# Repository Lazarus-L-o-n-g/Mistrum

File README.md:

# Mistrum
Mistrum is a legendary czechoslovak functional clone of famous ZX-Spectrum, more details at [8bit-replicas.com](https://www.8bit-replicas.com)

# Repository content
Here you can find schematics, PCB, gerber files, BOMs, binary content for memories and some ideas for build a replica.

# Main parts
- Rerouted PCB for replica of Mistrum computer (less vias and no additional wiring)
- PCB with original routing (500+ vias and ca. 40 wires)**
- PCB for PAL color video generator replica
- PCB for EPROM card replica**
- PCB for newly designed keyboard (Cherry MX extended keyboard)
- PCB for newly designed adapter to analog RGBi SCART or VGA 15kHz color video output
- PCB for newly designed adapter to standard ZX Spectrum system connector**

** will come later

**All schematics and PCBs are made using KiCad.**

## Extended Cherry MX Keyboard

The newly designed extended Cherry MX Keyboard features:
- Mechanical Cherry MX switches
- ZX Spectrum compatibility
- Optional bus or external power supply (external is deafult for Mistrum)
- Extended to separate cursors keys, delete key and special Mistrum keys (key Mistrum, NMI and RESET), realized as logic switches
- Two LED indicators, optional (for example BOOT, DRIVE)
- Two PCBs - main board and mask
- Identical size and mounting holes as PMD-85 coputer keyboard

## Adapter to analog RGBi or VGA 15kHz video output

This adapter outputs an analog RGB signal or VGA signal (15kHz only). It is designed mainly for color video output to RGB SCART capable TV and provides the high quality color video output.

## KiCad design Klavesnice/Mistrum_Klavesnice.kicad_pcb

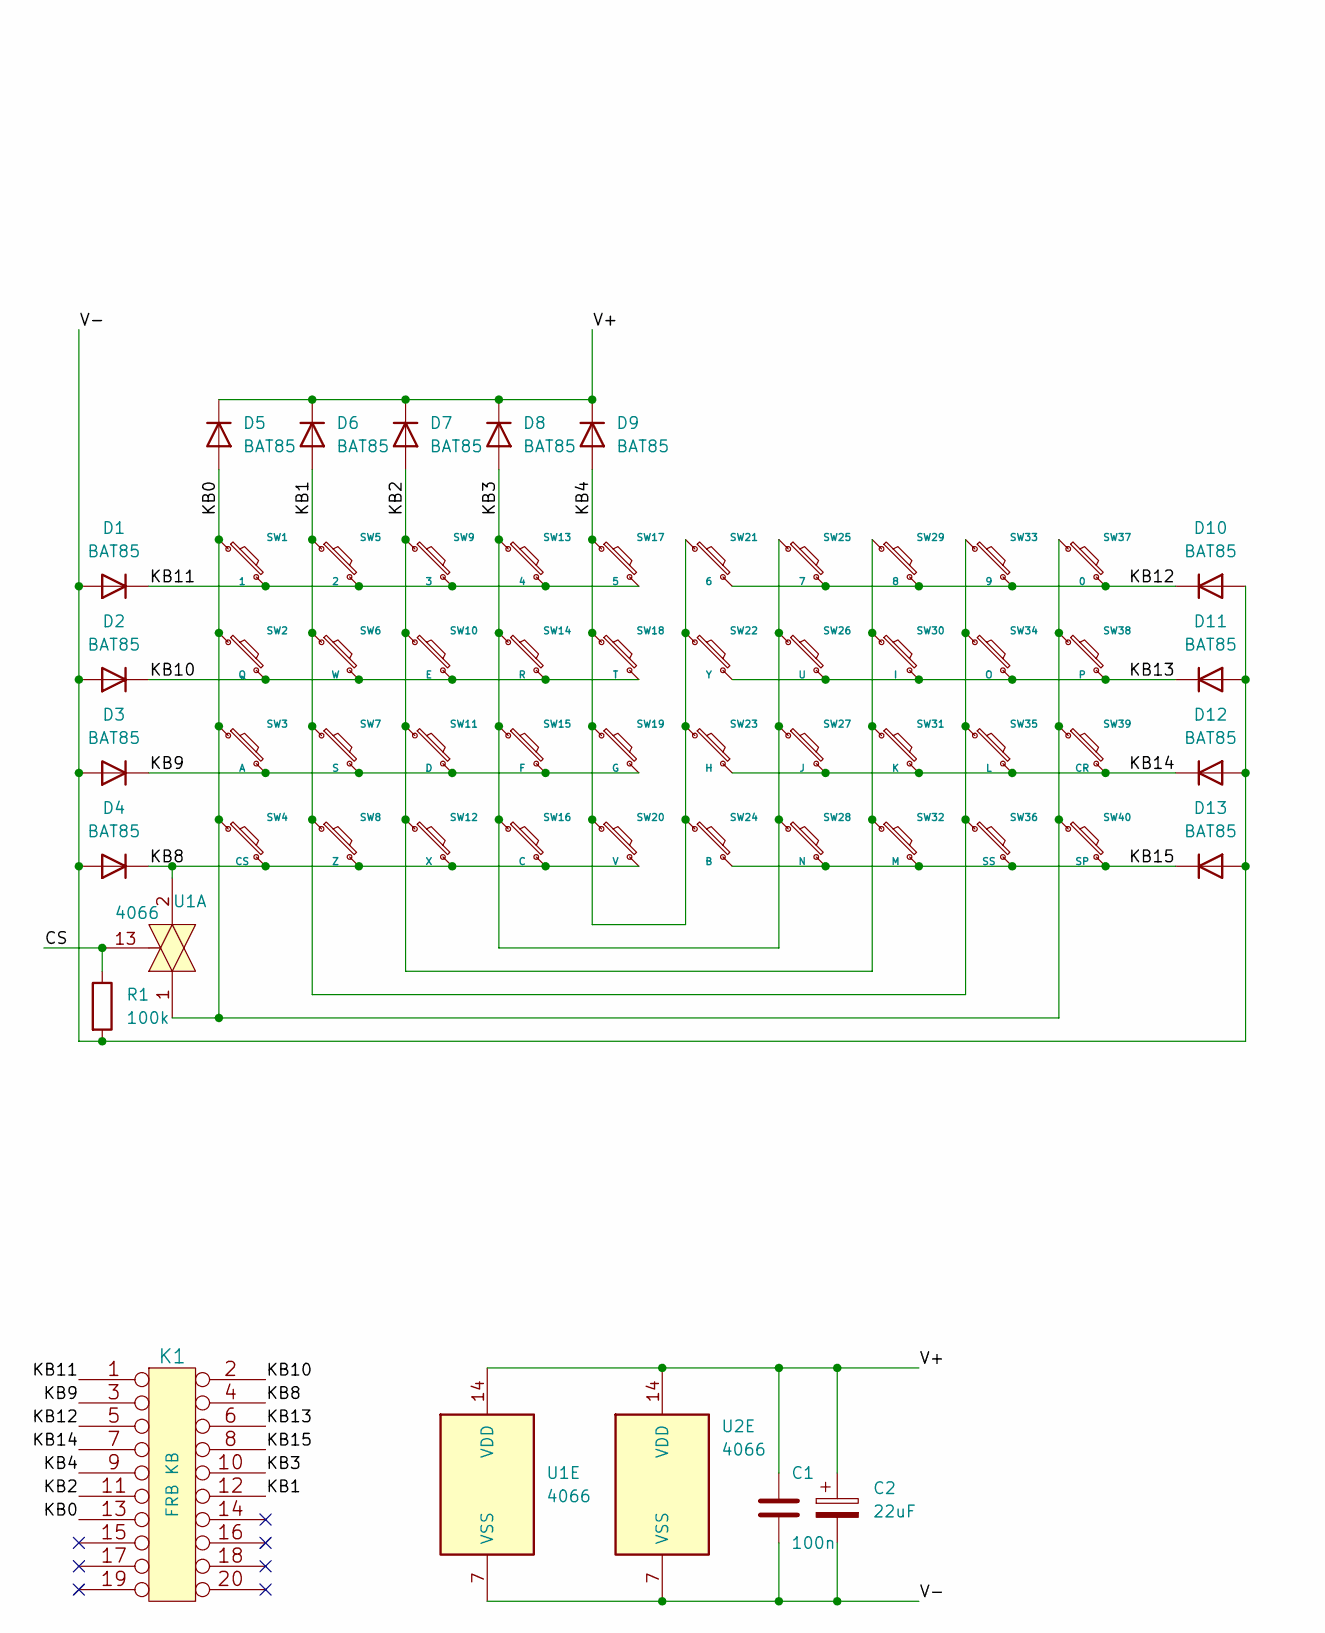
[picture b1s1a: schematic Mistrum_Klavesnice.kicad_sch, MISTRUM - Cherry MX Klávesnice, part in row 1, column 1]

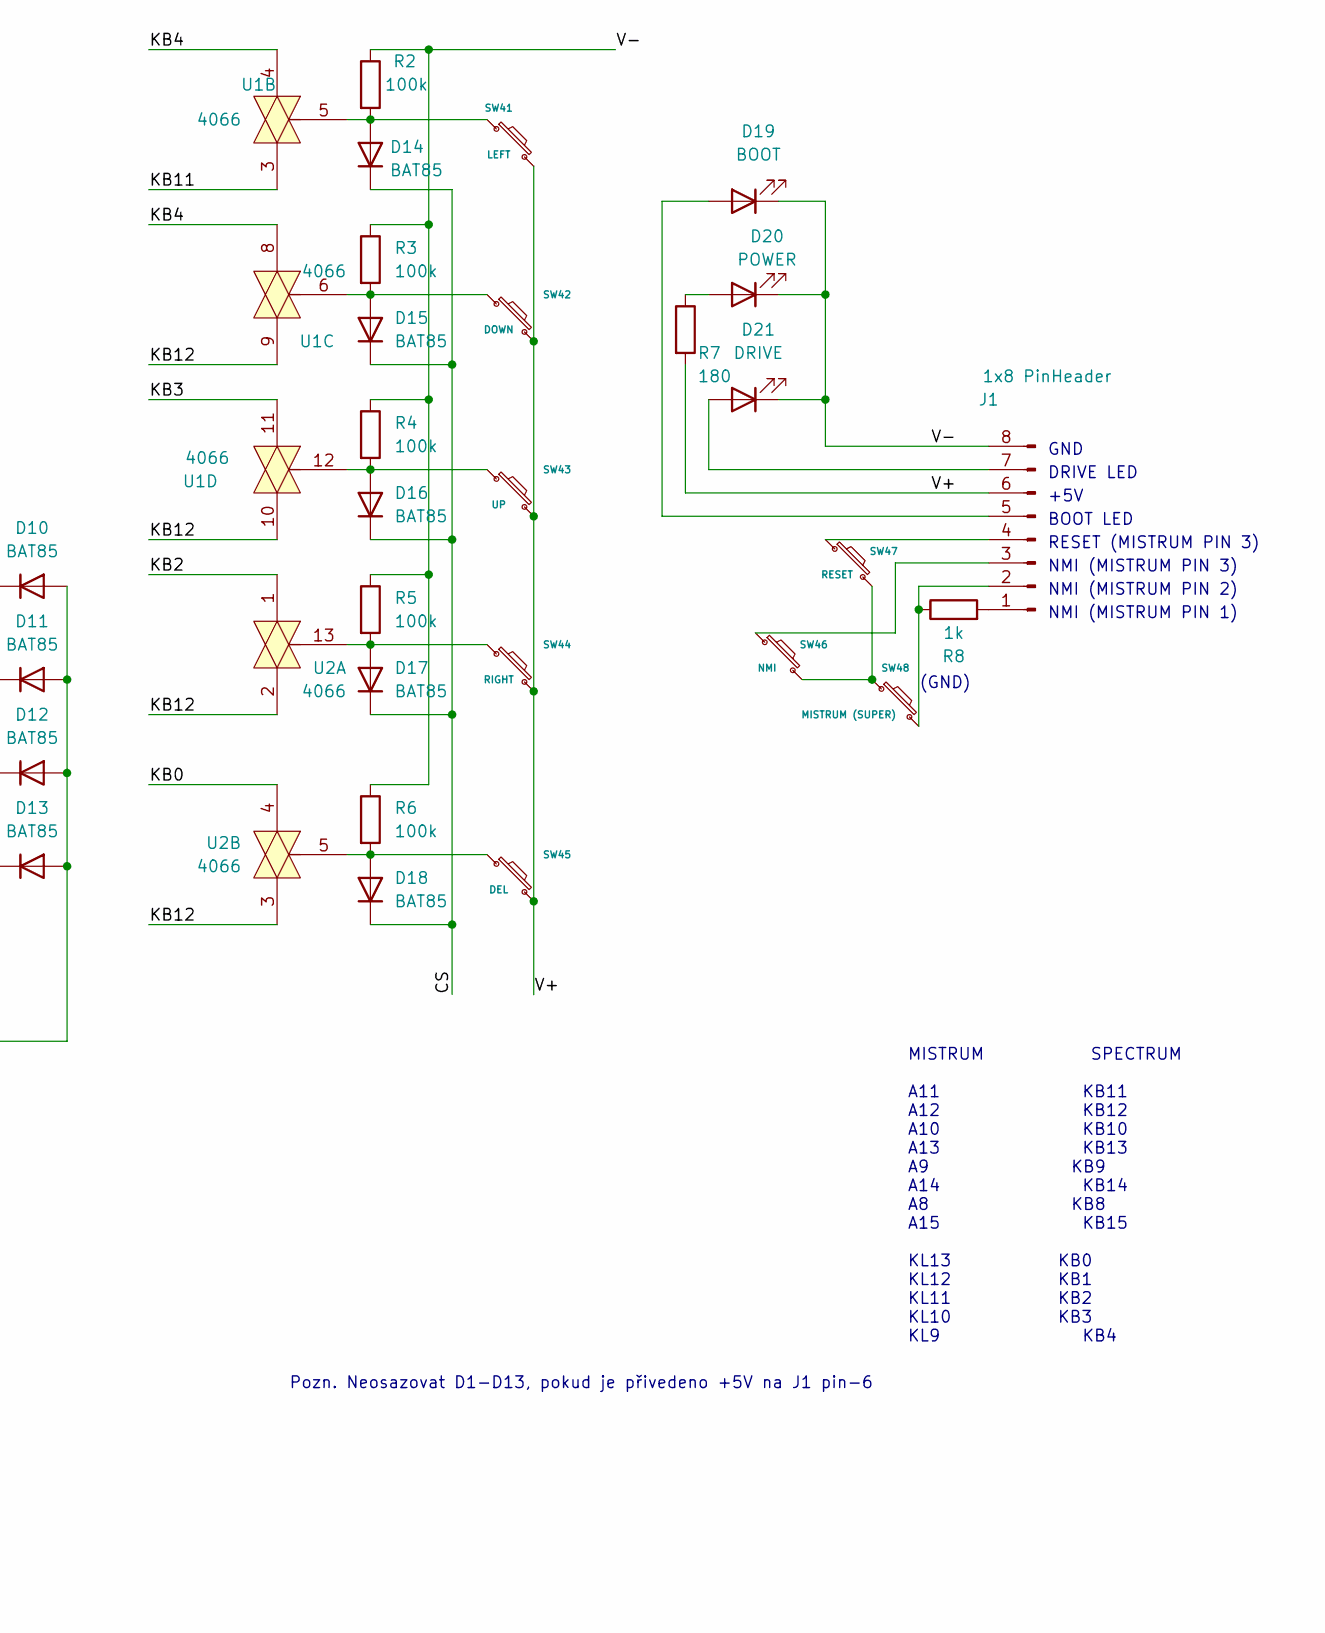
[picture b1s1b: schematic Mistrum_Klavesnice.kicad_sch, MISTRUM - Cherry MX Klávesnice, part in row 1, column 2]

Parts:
C1: 100n; C_Rect_L7.2mm_W3.5mm_P5.00mm_FKS2_FKP2_MKS2_MKP2
C2: 22uF; CP_Axial_L21.0mm_D8.0mm_P28.00mm_Horizontal
D1, D2, D3, D4, D5, D6, D7, D8, D9, D10, D11, D12, D13, D14, D15, D16, D17, D18: BAT85; D_DO-35_SOD27_P7.62mm_Horizontal
D19: BOOT; LED_D5.0mm
D20: POWER; LED_D5.0mm
D21: DRIVE; LED_D5.0mm
J1: 1x8 PinHeader; PinHeader_1x08_P2.54mm_Horizontal
K1: FRB KB; PinHeader_2x10_P2.54mm_Vertical
R1, R2, R3, R4, R5, R6: 100k; R_Axial_DIN0207_L6.3mm_D2.5mm_P7.62mm_Horizontal
R7: 180; R_Axial_DIN0207_L6.3mm_D2.5mm_P7.62mm_Horizontal
R8: 1k; R_Axial_DIN0207_L6.3mm_D2.5mm_P7.62mm_Horizontal
SW1: 1; SW_Cherry_MX_Mistrum
SW2: Q; SW_Cherry_MX_Mistrum
SW3: A; SW_Cherry_MX_Mistrum
SW4: CS; SW_Cherry_MX_Mistrum
SW5: 2; SW_Cherry_MX_Mistrum
SW6: W; SW_Cherry_MX_Mistrum
SW7: S; SW_Cherry_MX_Mistrum
SW8: Z; SW_Cherry_MX_Mistrum
SW9: 3; SW_Cherry_MX_Mistrum
SW10: E; SW_Cherry_MX_Mistrum
SW11: D; SW_Cherry_MX_Mistrum
SW12: X; SW_Cherry_MX_Mistrum
SW13: 4; SW_Cherry_MX_Mistrum
SW14: R; SW_Cherry_MX_Mistrum
SW15: F; SW_Cherry_MX_Mistrum
SW16: C; SW_Cherry_MX_Mistrum
SW17: 5; SW_Cherry_MX_Mistrum
SW18: T; SW_Cherry_MX_Mistrum
SW19: G; SW_Cherry_MX_Mistrum
SW20: V; SW_Cherry_MX_Mistrum
SW21: 6; SW_Cherry_MX_Mistrum
SW22: Y; SW_Cherry_MX_Mistrum
SW23: H; SW_Cherry_MX_Mistrum
SW24: B; SW_Cherry_MX_Mistrum
SW25: 7; SW_Cherry_MX_Mistrum
SW26: U; SW_Cherry_MX_Mistrum
SW27: J; SW_Cherry_MX_Mistrum
SW28: N; SW_Cherry_MX_Mistrum
SW29: 8; SW_Cherry_MX_Mistrum
SW30: I; SW_Cherry_MX_Mistrum
SW31: K; SW_Cherry_MX_Mistrum
SW32: M; SW_Cherry_MX_Mistrum
SW33: 9; SW_Cherry_MX_Mistrum
SW34: O; SW_Cherry_MX_Mistrum
SW35: L; SW_Cherry_MX_Mistrum
SW36: SS; SW_Cherry_MX_Mistrum
SW37: 0; SW_Cherry_MX_Mistrum
SW38: P; SW_Cherry_MX_Mistrum
SW39: CR; SW_Cherry_MX_Mistrum
SW40: SP; SW_Cherry_MX_Mistrum
SW41: LEFT; SW_Cherry_MX_Mistrum
SW42: DOWN; SW_Cherry_MX_Mistrum
SW43: UP; SW_Cherry_MX_Mistrum
SW44: RIGHT; SW_Cherry_MX_Mistrum
SW45: DEL; SW_Cherry_MX_Mistrum
SW46: NMI; SW_Cherry_MX_Mistrum
SW47: RESET; SW_Cherry_MX_Mistrum
SW48: MISTRUM (SUPER); SW_Cherry_MX_Mistrum
U1, U2: 4066; DIP-14_W7.62mm

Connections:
/CS: D14.1 (K), D15.1 (K), D16.1 (K), D17.1 (K), D18.1 (K), R1.1, U1.13
/KB0: D5.2 (A), K1.13, SW1.1, SW2.1, SW3.1, SW4.1, SW37.1, SW38.1, SW39.1, SW40.1, U1.1, U2.4
/KB1: D6.2 (A), K1.12, SW5.1, SW6.1, SW7.1, SW8.1, SW33.1, SW34.1, SW35.1, SW36.1
/KB2: D7.2 (A), K1.11, SW9.1, SW10.1, SW11.1, SW12.1, SW29.1, SW30.1, SW31.1, SW32.1, U2.1
/KB3: D8.2 (A), K1.10, SW13.1, SW14.1, SW15.1, SW16.1, SW25.1, SW26.1, SW27.1, SW28.1, U1.11
/KB4: D9.2 (A), K1.9, SW17.1, SW18.1, SW19.1, SW20.1, SW21.1, SW22.1, SW23.1, SW24.1, U1.4, U1.8
/KB8: D4.1 (K), K1.4, SW4.2, SW8.2, SW12.2, SW16.2, SW20.2, U1.2
/KB9: D3.1 (K), K1.3, SW3.2, SW7.2, SW11.2, SW15.2, SW19.2
/KB10: D2.1 (K), K1.2, SW2.2, SW6.2, SW10.2, SW14.2, SW18.2
/KB11: D1.1 (K), K1.1, SW1.2, SW5.2, SW9.2, SW13.2, SW17.2, U1.3
/KB12: D10.1 (K), K1.5, SW21.2, SW25.2, SW29.2, SW33.2, SW37.2, U1.9, U1.10, U2.2, U2.3
/KB13: D11.1 (K), K1.6, SW22.2, SW26.2, SW30.2, SW34.2, SW38.2
/KB14: D12.1 (K), K1.7, SW23.2, SW27.2, SW31.2, SW35.2, SW39.2
/KB15: D13.1 (K), K1.8, SW24.2, SW28.2, SW32.2, SW36.2, SW40.2
/V+: C1.1, C2.1, D5.1 (K), D6.1 (K), D7.1 (K), D8.1 (K), D9.1 (K), J1.6, R7.2, SW41.2, SW42.2, SW43.2, SW44.2, SW45.2, U1.14 (VDD), U2.14 (VDD)
/V-: C1.2, C2.2, D1.2 (A), D2.2 (A), D3.2 (A), D4.2 (A), D10.2 (A), D11.2 (A), D12.2 (A), D13.2 (A), D19.1 (K), D20.1 (K), D21.1 (K), J1.8, R1.2, R2.1, R3.1, R4.1, R5.1, R6.1, U1.7 (VSS), U2.7 (VSS)
unnamed: D14.2 (A), R2.2, SW41.1, U1.5
unnamed: D15.2 (A), R3.2, SW42.1, U1.6
unnamed: D16.2 (A), R4.2, SW43.1, U1.12
unnamed: D17.2 (A), R5.2, SW44.1, U2.13
unnamed: D18.2 (A), R6.2, SW45.1, U2.5
unnamed: D19.2 (A), J1.5
unnamed: D20.2 (A), R7.1
unnamed: D21.2 (A), J1.7
unnamed: J1.1, R8.2
unnamed: J1.2, R8.1, SW48.2
unnamed: J1.3, SW46.1
unnamed: J1.4, SW47.1
unnamed: SW46.2, SW47.2, SW48.1

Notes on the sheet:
+5V
GND
RESET (MISTRUM PIN 3)
NMI (MISTRUM PIN 2)
DRIVE LED
(GND)
MISTRUM SPECTRUM A11 KB11 A12 KB12 A10 KB10 A13 KB13 A9 KB9 A14 KB14 A8 KB8 A15 KB15 KL13 KB0 KL12 KB1 KL11 KB2 KL10 KB3 KL9 KB4
BOOT LED
NMI (MISTRUM PIN 1)
NMI (MISTRUM PIN 3)
Pozn. Neosazovat D1-D13, pokud je přivedeno +5V na J1 pin-6

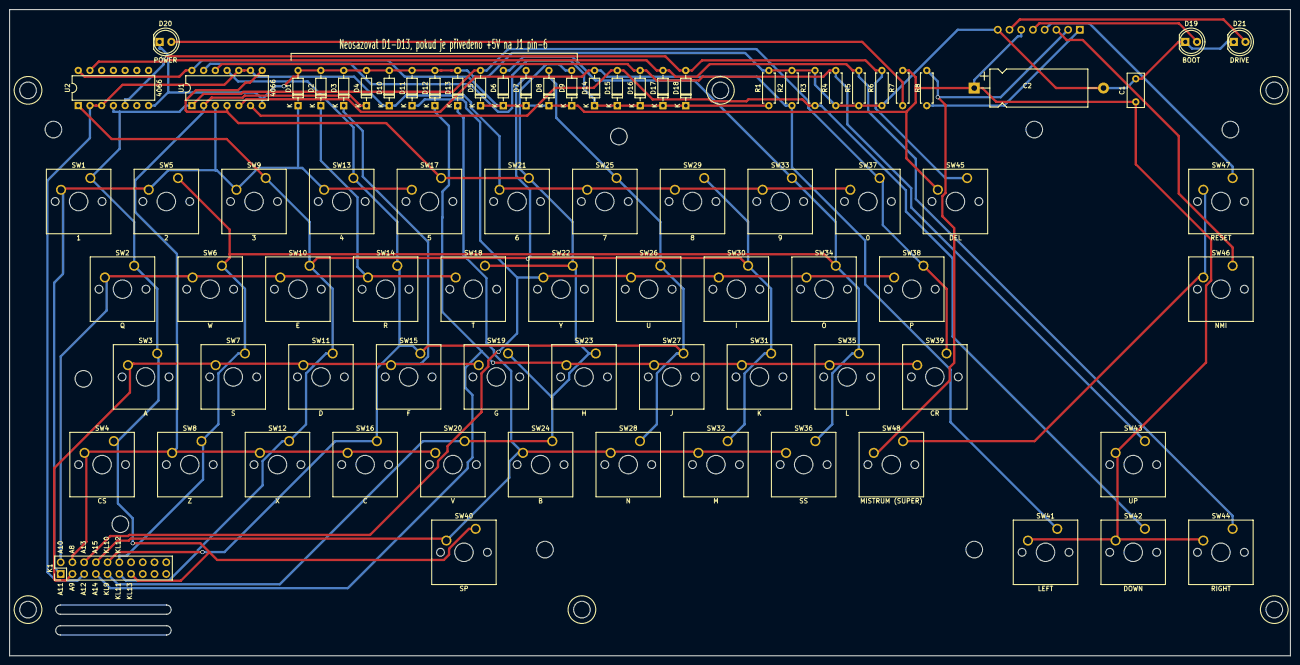
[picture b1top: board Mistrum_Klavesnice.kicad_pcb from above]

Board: 2 copper layers, 277.5 x 140.0 mm, 83 parts (1 on the bottom side), 29 nets.

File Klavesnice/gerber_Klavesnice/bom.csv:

Designator,Footprint,Quantity,Value,LCSC Part #
C1,C_Rect_L7.2mm_W3.5mm_P5.00mm_FKS2_FKP2_MKS2_MKP2,1,100n,
C2,CP_Axial_L21.0mm_D8.0mm_P28.00mm_Horizontal,1,22uF,
"D1, D10, D11, D12, D13, D14, D15, D16, D17, D18, D2, D3, D4, D5, D6, D7, D8, D9",D_DO-35_SOD27_P7.62mm_Horizontal,18,BAT85,
D19,LED_D5.0mm,1,BOOT,
D20,LED_D5.0mm,1,POWER,
D21,LED_D5.0mm,1,DRIVE,
J1,PinHeader_1x08_P2.54mm_Horizontal,1,1x8 PinHeader,
K1,PinHeader_2x10_P2.54mm_Vertical,1,FRB KB,
"R1, R2, R3, R4, R5, R6",R_Axial_DIN0207_L6.3mm_D2.5mm_P7.62mm_Horizontal,6,100k,
R7,R_Axial_DIN0207_L6.3mm_D2.5mm_P7.62mm_Horizontal,1,180,
R8,R_Axial_DIN0207_L6.3mm_D2.5mm_P7.62mm_Horizontal,1,1k,
SW1,SW_Cherry_MX_Mistrum,1,1,
SW10,SW_Cherry_MX_Mistrum,1,E,
SW11,SW_Cherry_MX_Mistrum,1,D,
SW12,SW_Cherry_MX_Mistrum,1,X,
SW13,SW_Cherry_MX_Mistrum,1,4,
SW14,SW_Cherry_MX_Mistrum,1,R,
SW15,SW_Cherry_MX_Mistrum,1,F,
SW16,SW_Cherry_MX_Mistrum,1,C,
SW17,SW_Cherry_MX_Mistrum,1,5,
SW18,SW_Cherry_MX_Mistrum,1,T,
SW19,SW_Cherry_MX_Mistrum,1,G,
SW2,SW_Cherry_MX_Mistrum,1,Q,
SW20,SW_Cherry_MX_Mistrum,1,V,
SW21,SW_Cherry_MX_Mistrum,1,6,
SW22,SW_Cherry_MX_Mistrum,1,Y,
SW23,SW_Cherry_MX_Mistrum,1,H,
SW24,SW_Cherry_MX_Mistrum,1,B,
SW25,SW_Cherry_MX_Mistrum,1,7,
SW26,SW_Cherry_MX_Mistrum,1,U,
SW27,SW_Cherry_MX_Mistrum,1,J,
SW28,SW_Cherry_MX_Mistrum,1,N,
SW29,SW_Cherry_MX_Mistrum,1,8,
SW3,SW_Cherry_MX_Mistrum,1,A,
SW30,SW_Cherry_MX_Mistrum,1,I,
SW31,SW_Cherry_MX_Mistrum,1,K,
SW32,SW_Cherry_MX_Mistrum,1,M,
SW33,SW_Cherry_MX_Mistrum,1,9,
SW34,SW_Cherry_MX_Mistrum,1,O,
SW35,SW_Cherry_MX_Mistrum,1,L,
SW36,SW_Cherry_MX_Mistrum,1,SS,
SW37,SW_Cherry_MX_Mistrum,1,0,
SW38,SW_Cherry_MX_Mistrum,1,P,
SW39,SW_Cherry_MX_Mistrum,1,CR,
SW4,SW_Cherry_MX_Mistrum,1,CS,
SW40,SW_Cherry_MX_Mistrum,1,SP,
SW41,SW_Cherry_MX_Mistrum,1,LEFT,
SW42,SW_Cherry_MX_Mistrum,1,DOWN,
SW43,SW_Cherry_MX_Mistrum,1,UP,
SW44,SW_Cherry_MX_Mistrum,1,RIGHT,
SW45,SW_Cherry_MX_Mistrum,1,DEL,
SW46,SW_Cherry_MX_Mistrum,1,NMI,
SW47,SW_Cherry_MX_Mistrum,1,RESET,
SW48,SW_Cherry_MX_Mistrum,1,MISTRUM (SUPER),
SW5,SW_Cherry_MX_Mistrum,1,2,
SW6,SW_Cherry_MX_Mistrum,1,W,
SW7,SW_Cherry_MX_Mistrum,1,S,
SW8,SW_Cherry_MX_Mistrum,1,Z,
SW9,SW_Cherry_MX_Mistrum,1,3,
"U1, U2",DIP-14_W7.62mm,2,4066,

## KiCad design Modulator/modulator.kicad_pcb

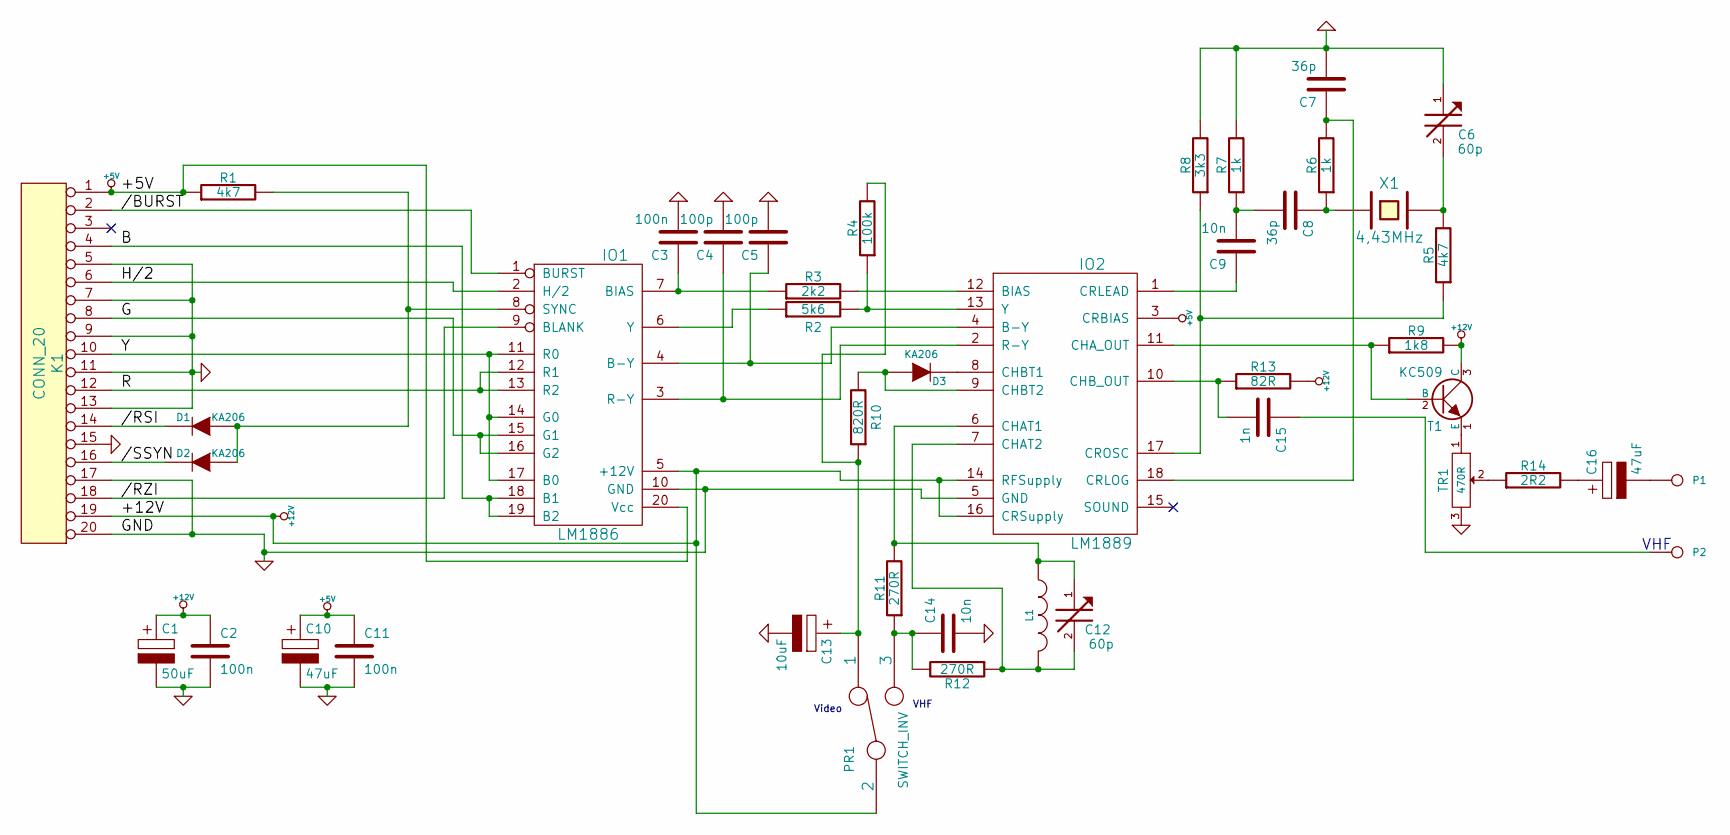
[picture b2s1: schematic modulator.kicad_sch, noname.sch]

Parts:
C1: 50uF
C2, C3, C11: 100n
C4, C5: 100p
C6, C12: 60p
C7, C8: 36p
C9, C14: 10n
C10, C16: 47uF
C13: 10uF
C15: 1n
D1, D2, D3: KA206
IO1: LM1886
IO2: LM1889
K1: CONN_20; TY5112011
L1: INDUCTOR
P1: CONN_1; Pin_D0.7mm_L6.5mm_W1.8mm_FlatFork
P2: CONN_1
PR1: SWITCH_INV
R1, R5: 4k7
R2: 5k6
R3: 2k2
R4: 100k
R6, R7: 1k
R8: 3k3
R9: 1k8
R10: 820R
R11, R12: 270R
R13: 82R
R14: 2R2
T1: KC509
TR1: 470R
X1: 4,43MHz

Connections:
+5V: C10.1, C11.1, IO1.20 (Vcc), IO2.3 (CRBIAS), K1.1, R1.1
+12V: C1.1, C2.1, IO1.5 (+12V), IO2.14 (RFSupply), IO2.16 (CRSupply), K1.19, PR1.2, R9.2, R13.2, T1.3 (C)
/B: IO1.18 (B1), IO1.19 (B2), K1.4
/G: IO1.15 (G1), IO1.16 (G2), K1.8
/H/2: IO1.2 (H/2), K1.6
/R: IO1.12 (R1), IO1.13 (R2), K1.12
/Y: IO1.11 (R0), IO1.14 (G0), IO1.17 (B0), K1.10
//BURST: IO1.1 (BURST), K1.2
//RSI: D1.2 (K), K1.14
//RZI: IO1.9 (BLANK), K1.18
//SSYN: D2.2 (K), K1.16
GND: C1.2, C2.2, C3.2, C4.2, C5.2, C6.1, C7.2, C10.2, C11.2, C13.2, C14.2, IO1.10 (GND), IO2.5 (GND), K1.5, K1.7, K1.9, K1.11, K1.13, K1.15, K1.17, K1.20, R7.2, R8.2, TR1.3
unnamed: C3.1, IO1.7 (BIAS), R3.1
unnamed: C4.1, IO1.3 (R-Y), IO2.2 (R-Y)
unnamed: C5.1, IO1.4 (B-Y), IO2.4 (B-Y)
unnamed: C6.2, R5.2, X1.2
unnamed: C7.1, IO2.18 (CRLOG), R6.2
unnamed: C8.1, R6.1, X1.1
unnamed: C8.2, C9.2, R7.1
unnamed: C9.1, IO2.1 (CRLEAD)
unnamed: C12.1, IO2.6 (CHAT1), L1.1, R11.2
unnamed: C12.2, IO2.7 (CHAT2), L1.2, R12.1
unnamed: C13.1, PR1.1, R4.2, R10.1
unnamed: C14.1, PR1.3, R11.1, R12.2
unnamed: C15.1, P2.1
unnamed: C15.2, IO2.10 (CHB_OUT), R13.1
unnamed: C16.1, R14.2
unnamed: C16.2, P1.1
unnamed: D1.1 (A), D2.1 (A), IO1.8 (SYNC), R1.2
unnamed: D3.1 (A), IO2.9 (CHBT2), R10.2
unnamed: D3.2 (K), IO2.8 (CHBT1)
unnamed: IO1.6 (Y), R2.1
unnamed: IO2.11 (CHA_OUT), R9.1, T1.2 (B)
unnamed: IO2.12 (BIAS), R3.2
unnamed: IO2.13 (Y), R2.2, R4.1
unnamed: IO2.17 (CROSC), R5.1, R8.1
unnamed: R14.1, TR1.2
unnamed: T1.1 (E), TR1.1

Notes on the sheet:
Video
VHF

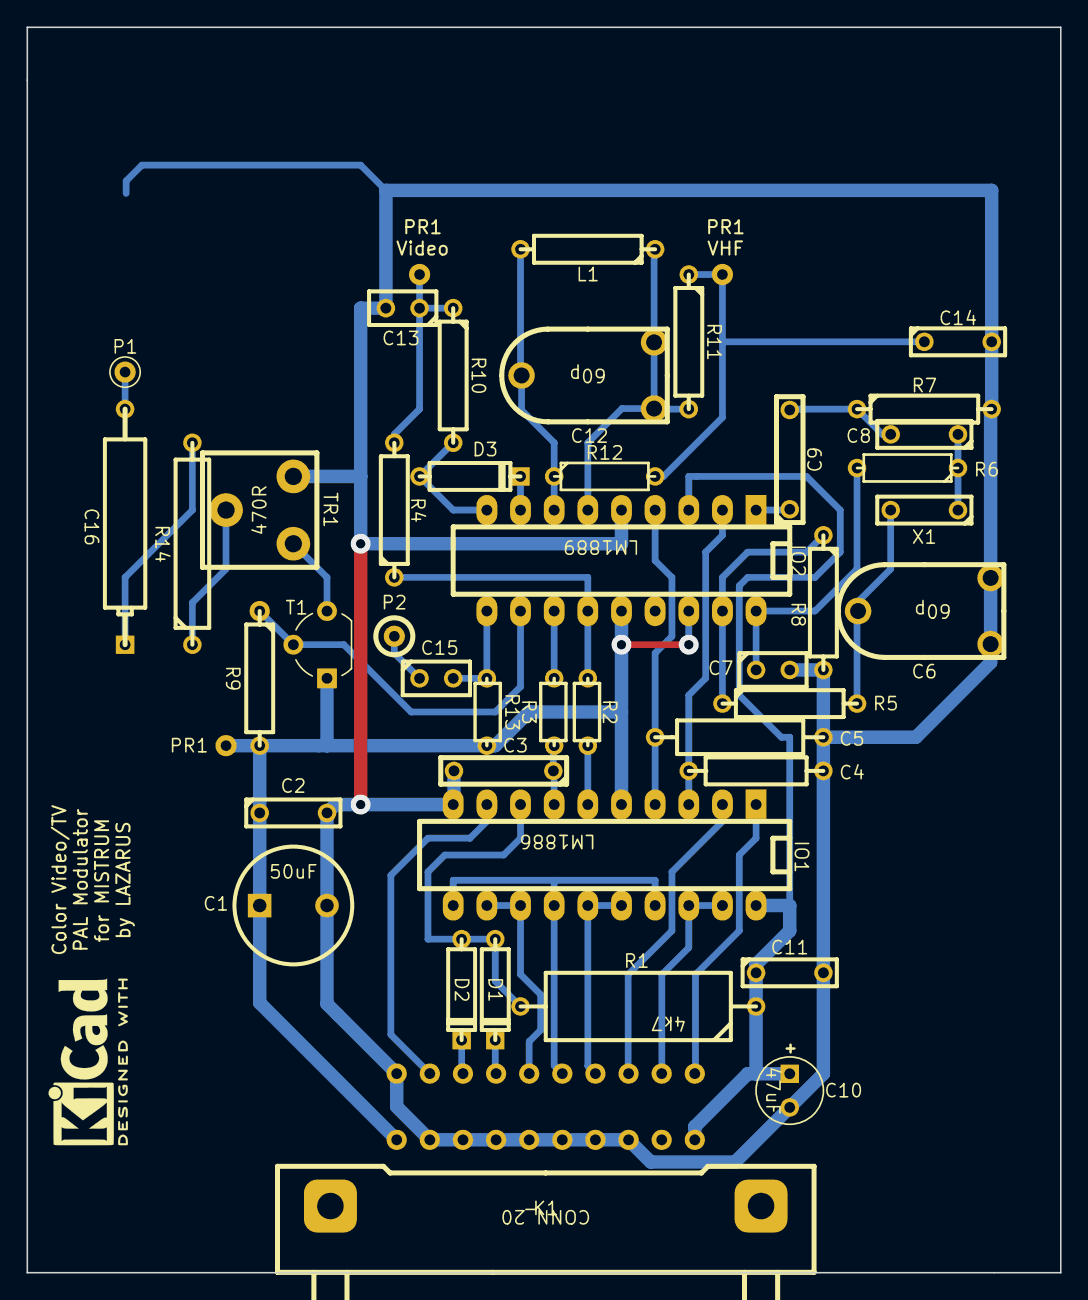
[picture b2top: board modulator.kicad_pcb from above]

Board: 2 copper layers, 78.0 x 94.0 mm, 43 parts (0 on the bottom side), 38 nets.

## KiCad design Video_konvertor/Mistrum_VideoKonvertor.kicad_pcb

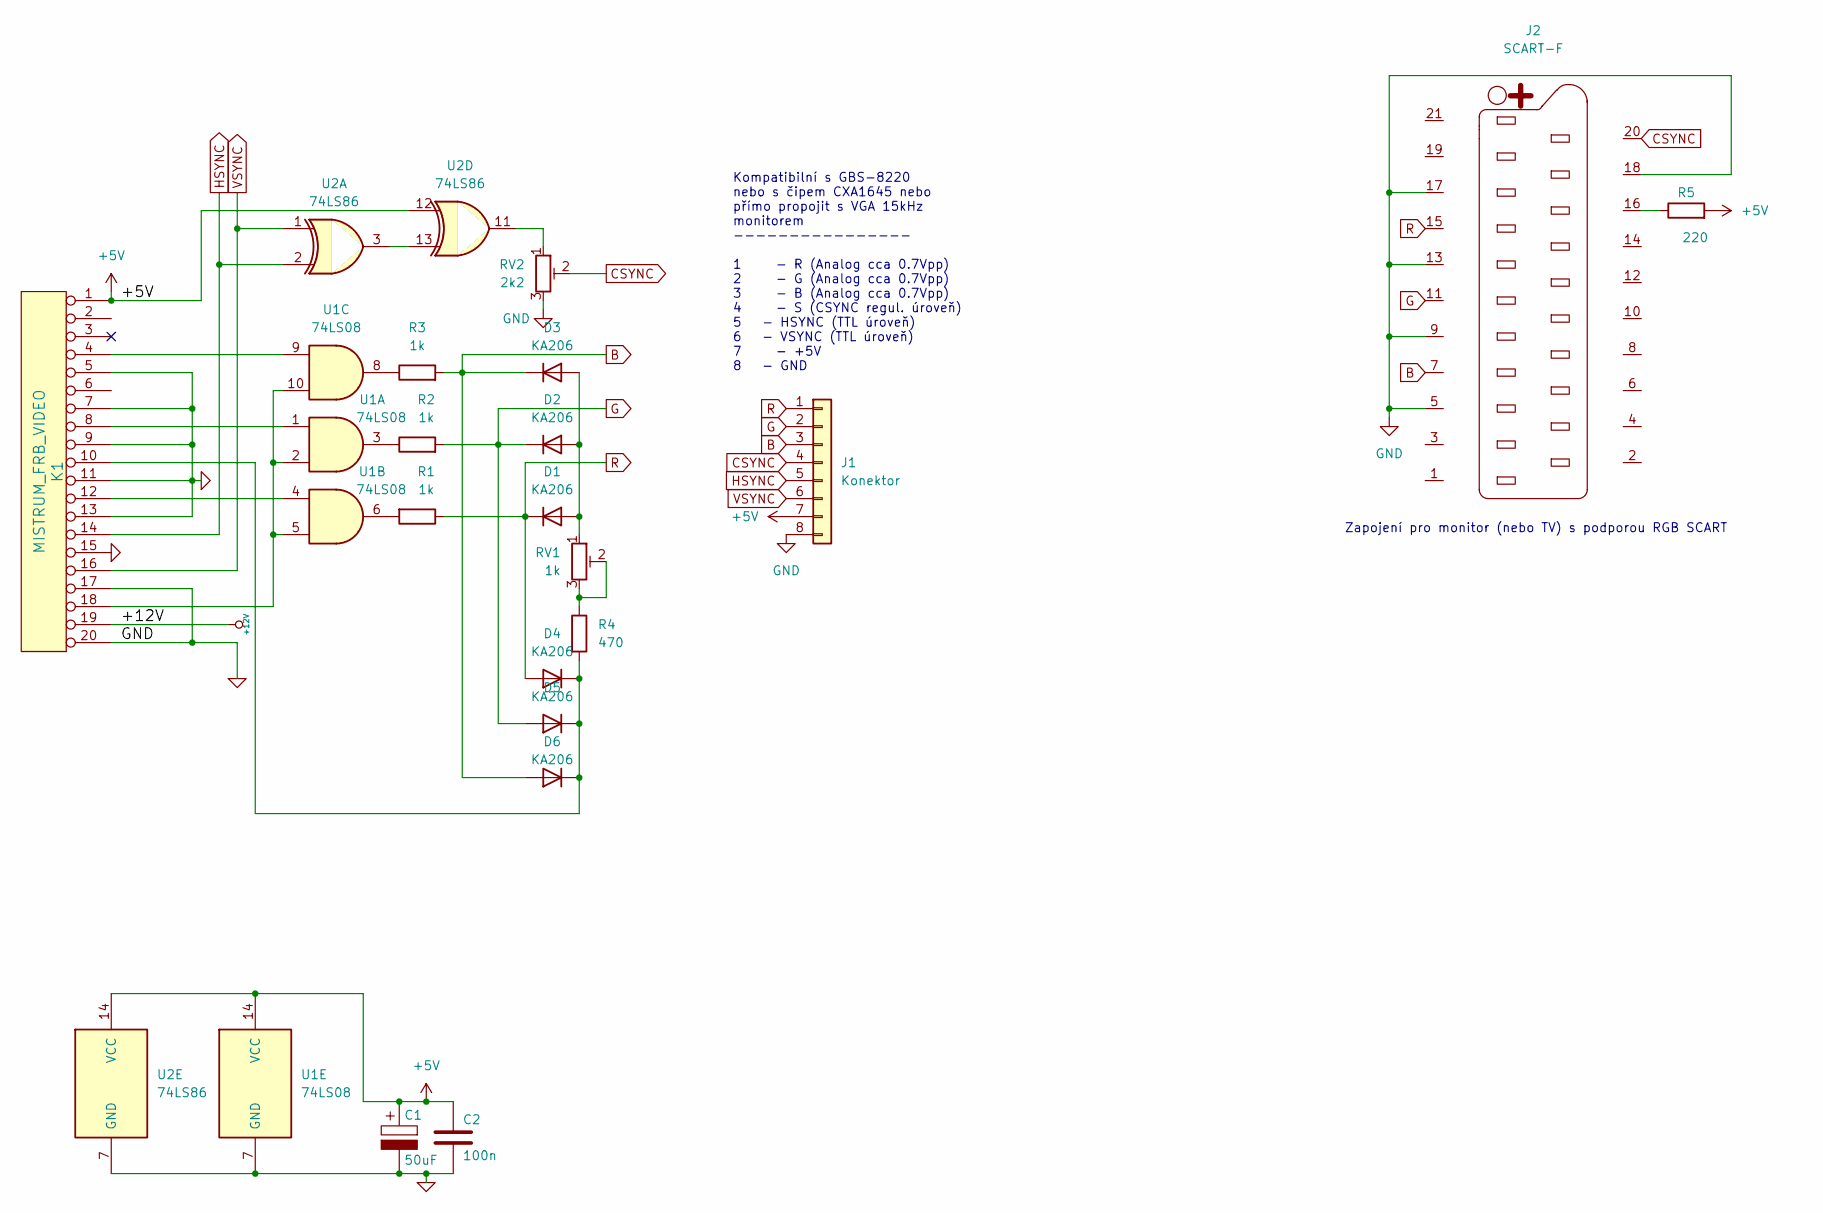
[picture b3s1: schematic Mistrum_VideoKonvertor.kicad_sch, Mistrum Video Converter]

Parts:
C1: 50uF; CP_Radial_D8.0mm_P3.50mm
C2: 100n; C_Disc_D5.0mm_W2.5mm_P5.00mm
D1, D2, D3, D4, D5, D6: KA206; D_DO-35_SOD27_P7.62mm_Horizontal
J1: Konektor; PinHeader_1x08_P2.54mm_Vertical
J2: SCART-F
K1: MISTRUM_FRB_VIDEO; TY5112011
R1, R2, R3: 1k; R_Axial_DIN0207_L6.3mm_D2.5mm_P7.62mm_Horizontal
R4: 470; R_Axial_DIN0207_L6.3mm_D2.5mm_P7.62mm_Horizontal
R5: 220
RV1: 1k; Pot_Trim_Round_6mm
RV2: 2k2; Pot_Trim_Round_6mm
U1: 74LS08; DIP-14_W7.62mm
U2: 74LS86; DIP-14_W7.62mm

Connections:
+5V: C1.1, C2.1, J1.7, K1.1, R5.2, U1.14 (VCC), U2.12, U2.14 (VCC)
+12V: K1.19
B: D3.1 (K), D6.2 (A), J1.3, J2.7, R3.2
CSYNC: J1.4, J2.20, RV2.2
G: D2.1 (K), D5.2 (A), J1.2, J2.11, R2.2
GND: C1.2, C2.2, J1.8, J2.5, J2.9, J2.13, J2.17, J2.18, K1.5, K1.7, K1.9, K1.11, K1.13, K1.15, K1.17, K1.20, RV2.3, U1.7 (GND), U2.7 (GND)
HSYNC: J1.5, K1.14, U2.2
unnamed: D1.2 (A), D2.2 (A), D3.2 (A), RV1.1
unnamed: D4.1 (K), D5.1 (K), D6.1 (K), K1.10, R4.2
unnamed: J2.16, R5.1
unnamed: K1.4, U1.9
unnamed: K1.8, U1.1
unnamed: K1.12, U1.4
unnamed: K1.18, U1.2, U1.5, U1.10
unnamed: R1.2, U1.6
unnamed: R2.1, U1.3
unnamed: R3.1, U1.8
unnamed: R4.1, RV1.2, RV1.3
unnamed: RV2.1, U2.11
unnamed: U2.3, U2.13
R: D1.1 (K), D4.2 (A), J1.1, J2.15, R1.1
VSYNC: J1.6, K1.16, U2.1

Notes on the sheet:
Kompatibilní s GBS-8220 nebo s čipem CXA1645 nebo přímo propojit s VGA 15kHz monitorem ---------------- 1 - R (Analog cca 0.7Vpp) 2 - G (Analog cca 0.7Vpp) 3 - B (Analog cca 0.7Vpp) 4 - S (CSYNC regul. úroveň) 5 - HSYNC (TTL úroveň) 6 - VSYNC (TTL úroveň) 7 - +5V 8 - GND
Zapojení pro monitor (nebo TV) s podporou RGB SCART

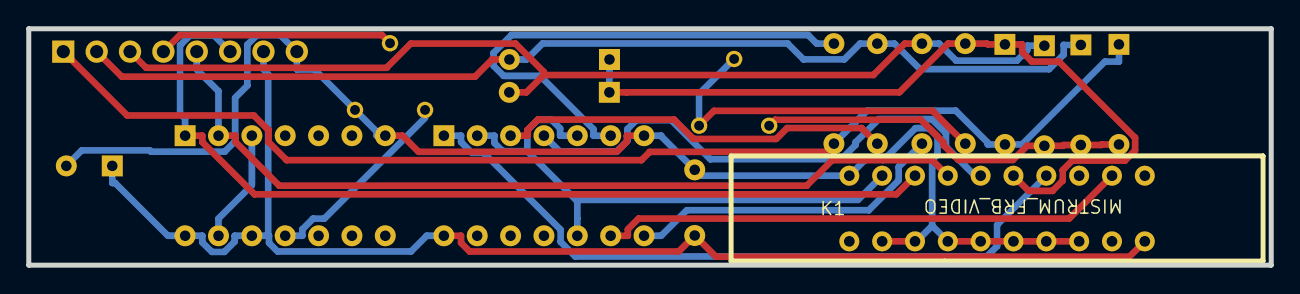
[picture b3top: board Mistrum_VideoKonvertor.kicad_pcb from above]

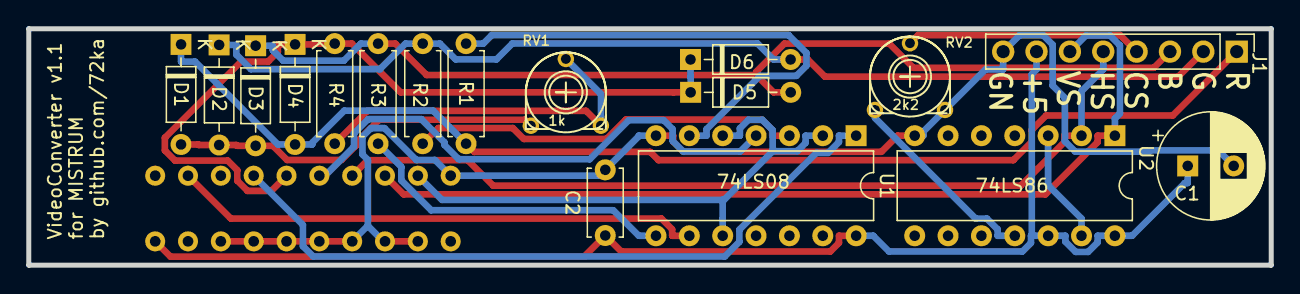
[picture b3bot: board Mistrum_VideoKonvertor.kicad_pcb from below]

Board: 2 copper layers, 94.6 x 18.0 mm, 18 parts (17 on the bottom side), 20 nets.

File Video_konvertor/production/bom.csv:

Designator,Footprint,Quantity,Value,LCSC Part #
K1,TY5112011,1,MISTRUM_FRB_VIDEO,
D1,D_DO-35_SOD27_P7.62mm_Horizontal,1,KA206,
R4,R_Axial_DIN0207_L6.3mm_D2.5mm_P7.62mm_Horizontal,1,470,
R1,R_Axial_DIN0207_L6.3mm_D2.5mm_P7.62mm_Horizontal,1,1k,
D4,D_DO-35_SOD27_P7.62mm_Horizontal,1,KA206,
RV1,Pot_Trim_Round_6mm,1,1k,
RV2,Pot_Trim_Round_6mm,1,2k2,
R3,R_Axial_DIN0207_L6.3mm_D2.5mm_P7.62mm_Horizontal,1,1k,
U1,DIP-14_W7.62mm,1,74LS08,
C2,C_Disc_D5.0mm_W2.5mm_P5.00mm,1,100n,
D2,D_DO-35_SOD27_P7.62mm_Horizontal,1,KA206,
C1,CP_Radial_D8.0mm_P3.50mm,1,50uF,
D6,D_DO-35_SOD27_P7.62mm_Horizontal,1,KA206,
R2,R_Axial_DIN0207_L6.3mm_D2.5mm_P7.62mm_Horizontal,1,1k,
D5,D_DO-35_SOD27_P7.62mm_Horizontal,1,KA206,
J1,PinHeader_1x08_P2.54mm_Vertical,1,Konektor,
D3,D_DO-35_SOD27_P7.62mm_Horizontal,1,KA206,
U2,DIP-14_W7.62mm,1,74LS86,

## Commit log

2021-08-17 KiCad files for replica
2021-08-17 add Gerbers, Images BOM
2021-08-22 Create LICENSE
2021-08-22 Added missing files
2021-08-22 Added sockets to BOM
2021-08-22 Binary and HEX files for PROM/EPROM
2021-08-22 Binary content for IO113 - 74188
2021-08-22 Binary content in HEX format for IO113 - 74188
2021-08-22 Binary content for IO52 - 74S571
2021-08-22 Binary content in HEX format for IO52 - 74S571
2021-08-22 Binary content for EPROM - standard ZX Spectrum ROM
2021-08-22 Binary content for EPROM - original MISTRUM ROM
2022-02-05 Color Video/TV Modulator
2022-02-05 Updated BOM links
2022-02-06 Modulator update
2022-02-06 Modulator BOM update
2022-02-06 ROM updates
2024-04-25 Added MISTRUM Keyboard
    New special Cherry MX extended Keyboard for Mistrum. Compatible with ZX Spectrum and clones.
2024-04-25 Add RGBi video converter
    Newly developed video converter which fixes and converts MISTRUM TTL RGB output to RGBi video signal. The output is compatible with SCART TV input or 15kHz VGA monitor.
2024-04-25 Added Videoconvertor
    Update. With schematic and images.
